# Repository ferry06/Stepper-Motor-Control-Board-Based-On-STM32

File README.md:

# Stepper-Motor-Control-Board-Based-On-STM32

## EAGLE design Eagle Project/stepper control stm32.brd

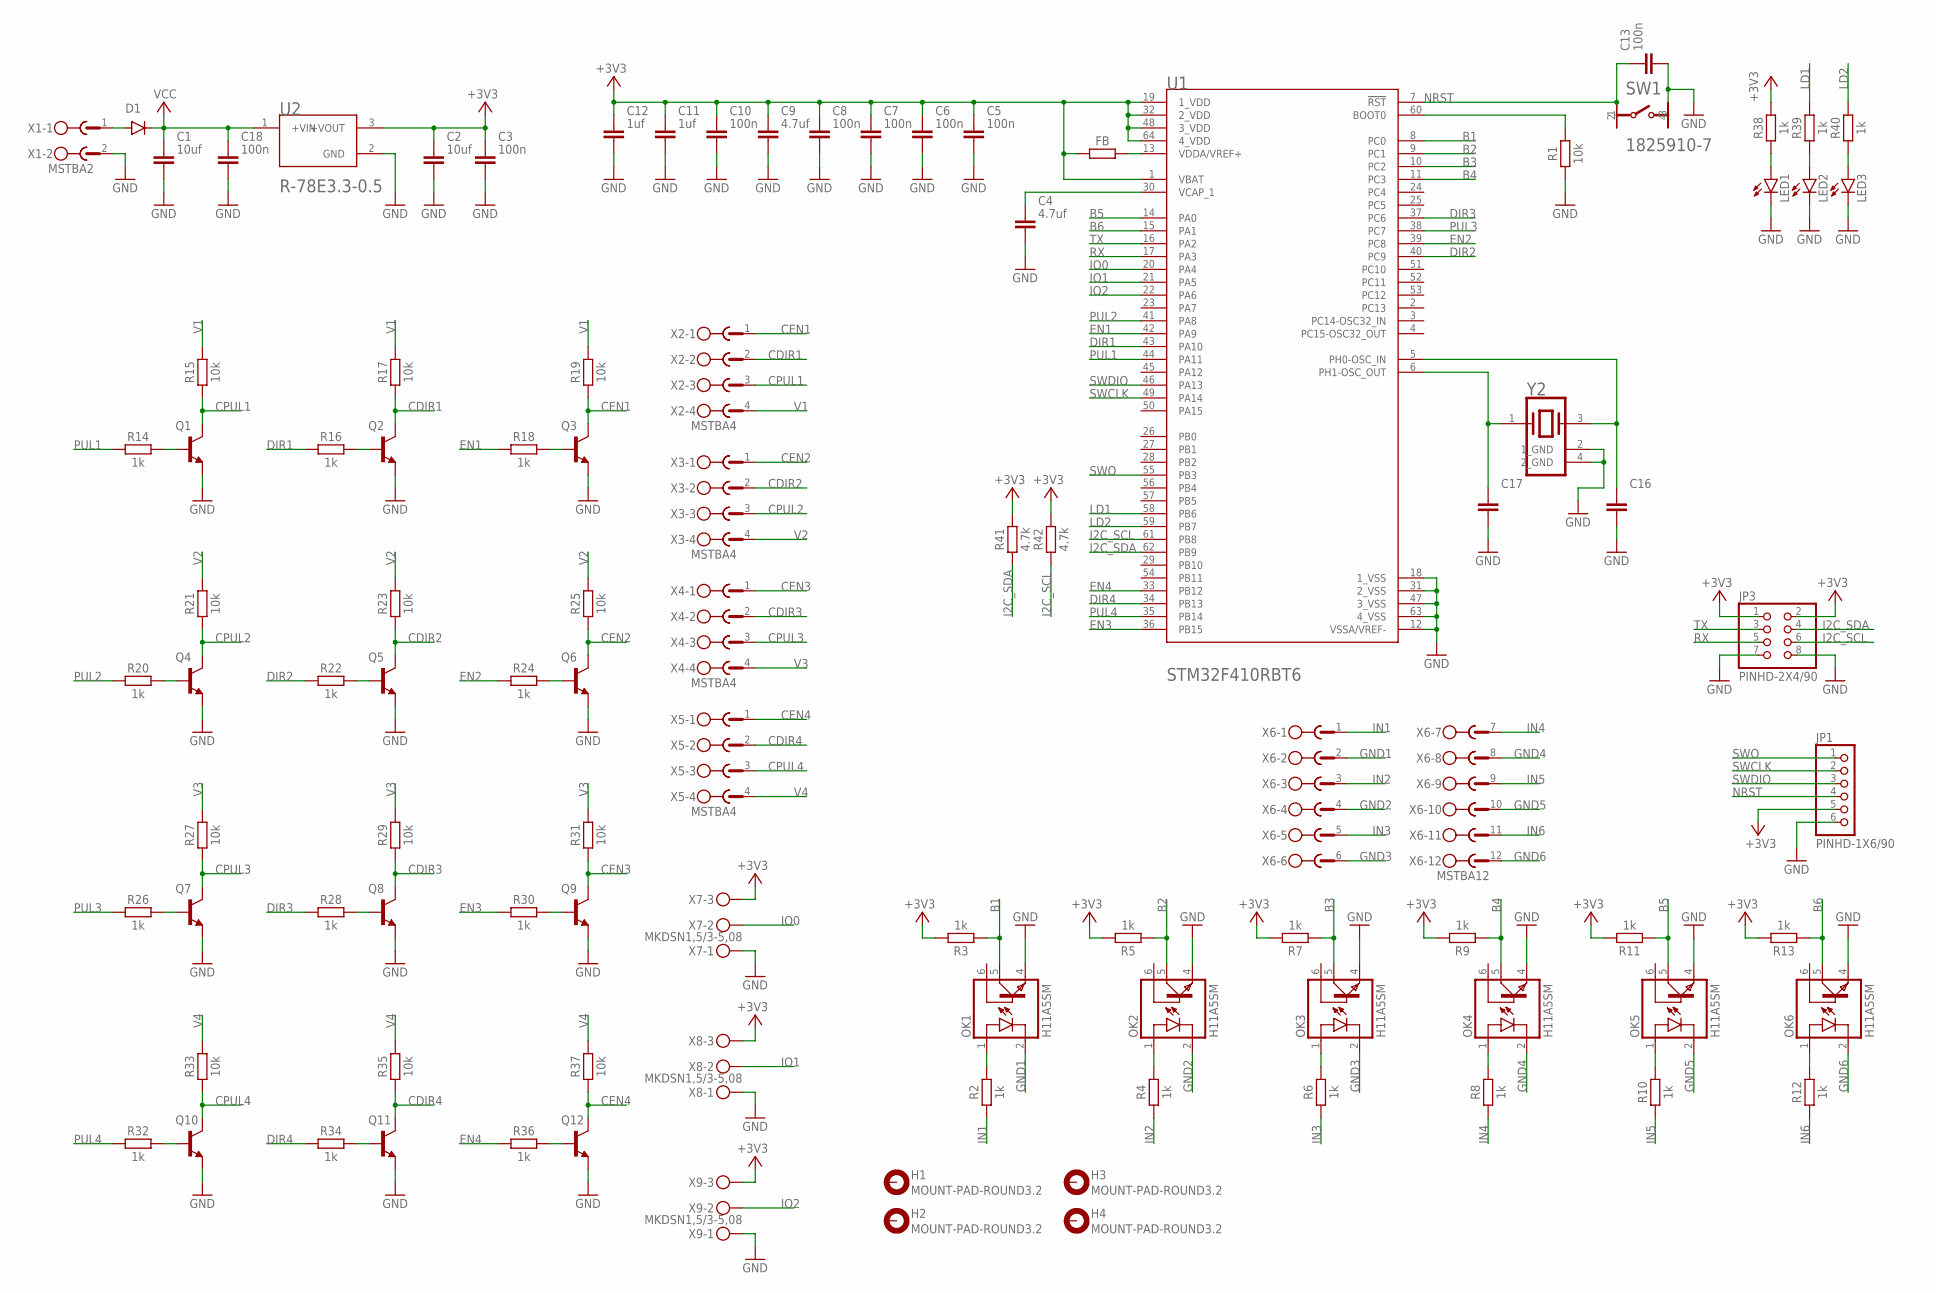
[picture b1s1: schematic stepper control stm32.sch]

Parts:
C1, C2: 10uf; CAPC2012X110
C3, C5, C6, C7, C8, C10, C13, C18: 100n; CAPC1608X85
C4, C9: 4.7uf; CAPC3216X135
C11, C12: 1uf; CAPC1608X85
C16, C17: C_CHIP-0603(1608-METRIC); CAPC1608X85
D1: DIODE-SOD123; SOD123
FB: R_CHIP-0402(1005-METRIC); RESC1005X40
H1, H2, H3, H4: MOUNT-PAD-ROUND3.2; 3,2-PAD
JP1: PINHD-1X6/90; 1X06/90
JP3: PINHD-2X4/90; 2X04/90
LED1, LED2, LED3: LEDCHIPLED_0805; CHIPLED_0805
OK1, OK2, OK3, OK4, OK5, OK6: H11A5SM; DIL6-SMD
Q1, Q2, Q3, Q4, Q5, Q6, Q7, Q8, Q9, Q10, Q11, Q12: MMBT3904LT1G; SOT23-3
R1, R15, R17, R19, R21, R23, R25, R27, R29, R31, R33, R35, R37: 10k; RESC1608X60
R2, R3, R4, R5, R6, R7, R8, R9, R10, R11, R12, R13, R14, R16, R18, R20, R22, R24, R26, R28, R30, R32, R34, R36, R38, R39, R40: 1k; RESC1608X60
R41, R42: 4.7k; RESC1608X60
SW1: TE_1825910-7TE_1825910-7_0_0; TE_1825910-7_0
U1: STMICROELECTRONICS_STM32F410RBT6STMICROELECTRONIC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; STMICROELECTRONICS_STM32F410RBT6_1
U2: RECOM_R-78E3.3-0.5RECOM_R-78E3.3-0.5_0_0; RECOM_R-78E3.3-0.5_0
X1: MSTBA2
X2, X3, X4, X5: MSTBA4
X6: MSTBA12
X7, X8, X9: MKDSN1,5/3-5,08
Y2: ABRACON_ABM8G-25.000MHZ-18-D2Y-TABRACON_ABM8G-25.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; ABRACON_ABM8G-25.000MHZ-18-D2Y-T_0

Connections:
+3V3: C2.1, C3.1, C5.1, C6.1, C7.1, C8.1, C9.1, C10.1, C11.1, C12.1, FB.1, JP1.5, JP3.1, JP3.2, R3.2, R5.2, R7.2, R9.2, R11.2, R13.2, R38.2, R41.2, R42.2, U1.1 (VBAT), U1.19 (1_VDD), U1.32 (2_VDD), U1.48 (3_VDD), U1.64 (4_VDD), U2.3 (+VOUT), X7.3, X8.3, X9.3
B1: OK1.5 (COL), R3.1, U1.8 (PC0)
B2: OK2.5 (COL), R5.1, U1.9 (PC1)
B3: OK3.5 (COL), R7.1, U1.10 (PC2)
B4: OK4.5 (COL), R9.1, U1.11 (PC3)
B5: OK5.5 (COL), R11.1, U1.14 (PA0)
B6: OK6.5 (COL), R13.1, U1.15 (PA1)
CDIR1: Q2.3 (C), R17.1, X2.2
CDIR2: Q5.3 (C), R23.1, X3.2
CDIR3: Q8.3 (C), R29.1, X4.2
CDIR4: Q11.3 (C), R35.1, X5.2
CEN1: Q3.3 (C), R19.1, X2.1
CEN2: Q6.3 (C), R25.1, X3.1
CEN3: Q9.3 (C), R31.1, X4.1
CEN4: Q12.3 (C), R37.1, X5.1
CPUL1: Q1.3 (C), R15.1, X2.3
CPUL2: Q4.3 (C), R21.1, X3.3
CPUL3: Q7.3 (C), R27.1, X4.3
CPUL4: Q10.3 (C), R33.1, X5.3
DIR1: R16.1, U1.43 (PA10)
DIR2: R22.1, U1.40 (PC9)
DIR3: R28.1, U1.37 (PC6)
DIR4: R34.1, U1.34 (PB13)
EN1: R18.1, U1.42 (PA9)
EN2: R24.1, U1.39 (PC8)
EN3: R30.1, U1.36 (PB15)
EN4: R36.1, U1.33 (PB12)
GND: C1.2, C2.2, C3.2, C4.2, C5.2, C6.2, C7.2, C8.2, C9.2, C10.2, C11.2, C12.2, C13.2, C16.2, C17.2, C18.2, JP1.6, JP3.7, JP3.8, LED1.C, LED2.C, LED3.C, OK1.4 (EMI), OK2.4 (EMI), OK3.4 (EMI), OK4.4 (EMI), OK5.4 (EMI), OK6.4 (EMI), Q1.2 (E), Q2.2 (E), Q3.2 (E), Q4.2 (E), Q5.2 (E), Q6.2 (E), Q7.2 (E), Q8.2 (E), Q9.2 (E), Q10.2 (E), Q11.2 (E), Q12.2 (E), R1.1, SW1.3, U1.12 (VSSA/VREF-), U1.18 (1_VSS), U1.31 (2_VSS), U1.47 (3_VSS), U1.63 (4_VSS), U2.2 (GND), X1.2, X7.1, X8.1, X9.1, Y2.2 (1_GND), Y2.4 (2_GND)
GND1: OK1.2 (C), X6.2
GND2: OK2.2 (C), X6.4
GND3: OK3.2 (C), X6.6
GND4: OK4.2 (C), X6.8
GND5: OK5.2 (C), X6.10
GND6: OK6.2 (C), X6.12
I2C_SCL: JP3.6, R42.1, U1.61 (PB8)
I2C_SDA: JP3.4, R41.1, U1.62 (PB9)
IN1: R2.1, X6.1
IN2: R4.1, X6.3
IN3: R6.1, X6.5
IN4: R8.1, X6.7
IN5: R10.1, X6.9
IN6: R12.1, X6.11
IO0: U1.20 (PA4), X7.2
IO1: U1.21 (PA5), X8.2
IO2: U1.22 (PA6), X9.2
LD1: R39.2, U1.58 (PB6)
LD2: R40.2, U1.59 (PB7)
unnamed: FB.2, U1.13 (VDDA/VREF+)
unnamed: C4.1, U1.30 (VCAP_1)
unnamed: R1.2, U1.60 (BOOT0)
unnamed: C16.1, U1.5 (PH0-OSC_IN), Y2.3
unnamed: C17.1, U1.6 (PH1-OSC_OUT), Y2.1
unnamed: OK1.1 (A), R2.2
unnamed: Q1.1 (B), R14.2
unnamed: LED3.A, R40.1
unnamed: LED2.A, R39.1
unnamed: OK2.1 (A), R4.2
unnamed: Q10.1 (B), R32.2
unnamed: Q2.1 (B), R16.2
unnamed: LED1.A, R38.1
unnamed: OK3.1 (A), R6.2
unnamed: D1.A, X1.1
unnamed: Q3.1 (B), R18.2
unnamed: OK4.1 (A), R8.2
unnamed: OK5.1 (A), R10.2
unnamed: Q4.1 (B), R20.2
unnamed: OK6.1 (A), R12.2
unnamed: Q5.1 (B), R22.2
unnamed: Q11.1 (B), R34.2
unnamed: Q6.1 (B), R24.2
unnamed: Q7.1 (B), R26.2
unnamed: Q8.1 (B), R28.2
unnamed: Q9.1 (B), R30.2
unnamed: Q12.1 (B), R36.2
NRST: C13.1, JP1.4, SW1.1, U1.7 (!RST!)
PUL1: R14.1, U1.44 (PA11)
PUL2: R20.1, U1.41 (PA8)
PUL3: R26.1, U1.38 (PC7)
PUL4: R32.1, U1.35 (PB14)
RX: JP3.5, U1.17 (PA3)
SWCLK: JP1.2, U1.49 (PA14)
SWDIO: JP1.3, U1.46 (PA13)
SWO: JP1.1, U1.55 (PB3)
TX: JP3.3, U1.16 (PA2)
V1: R15.2, R17.2, R19.2, X2.4
V2: R21.2, R23.2, R25.2, X3.4
V3: R27.2, R29.2, R31.2, X4.4
V4: R33.2, R35.2, R37.2, X5.4
VCC: C1.1, C18.1, D1.C, U2.1 (+VIN)

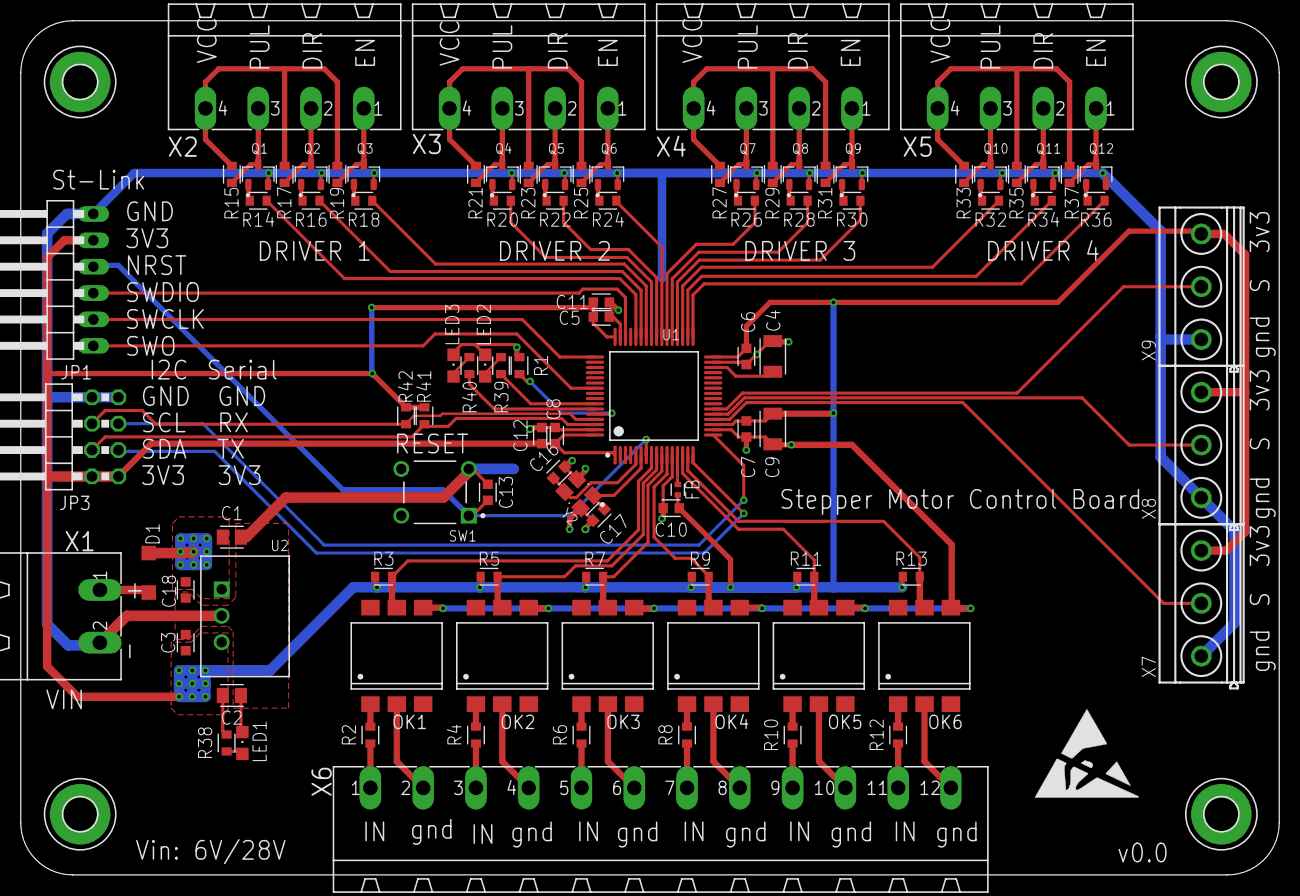
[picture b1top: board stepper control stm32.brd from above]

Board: 2 copper layers, 121.1 x 82.2 mm, 101 parts (0 on the bottom side), 89 nets.

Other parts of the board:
U$1: ESD_10.00

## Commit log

2020-11-07 Create Read Me
